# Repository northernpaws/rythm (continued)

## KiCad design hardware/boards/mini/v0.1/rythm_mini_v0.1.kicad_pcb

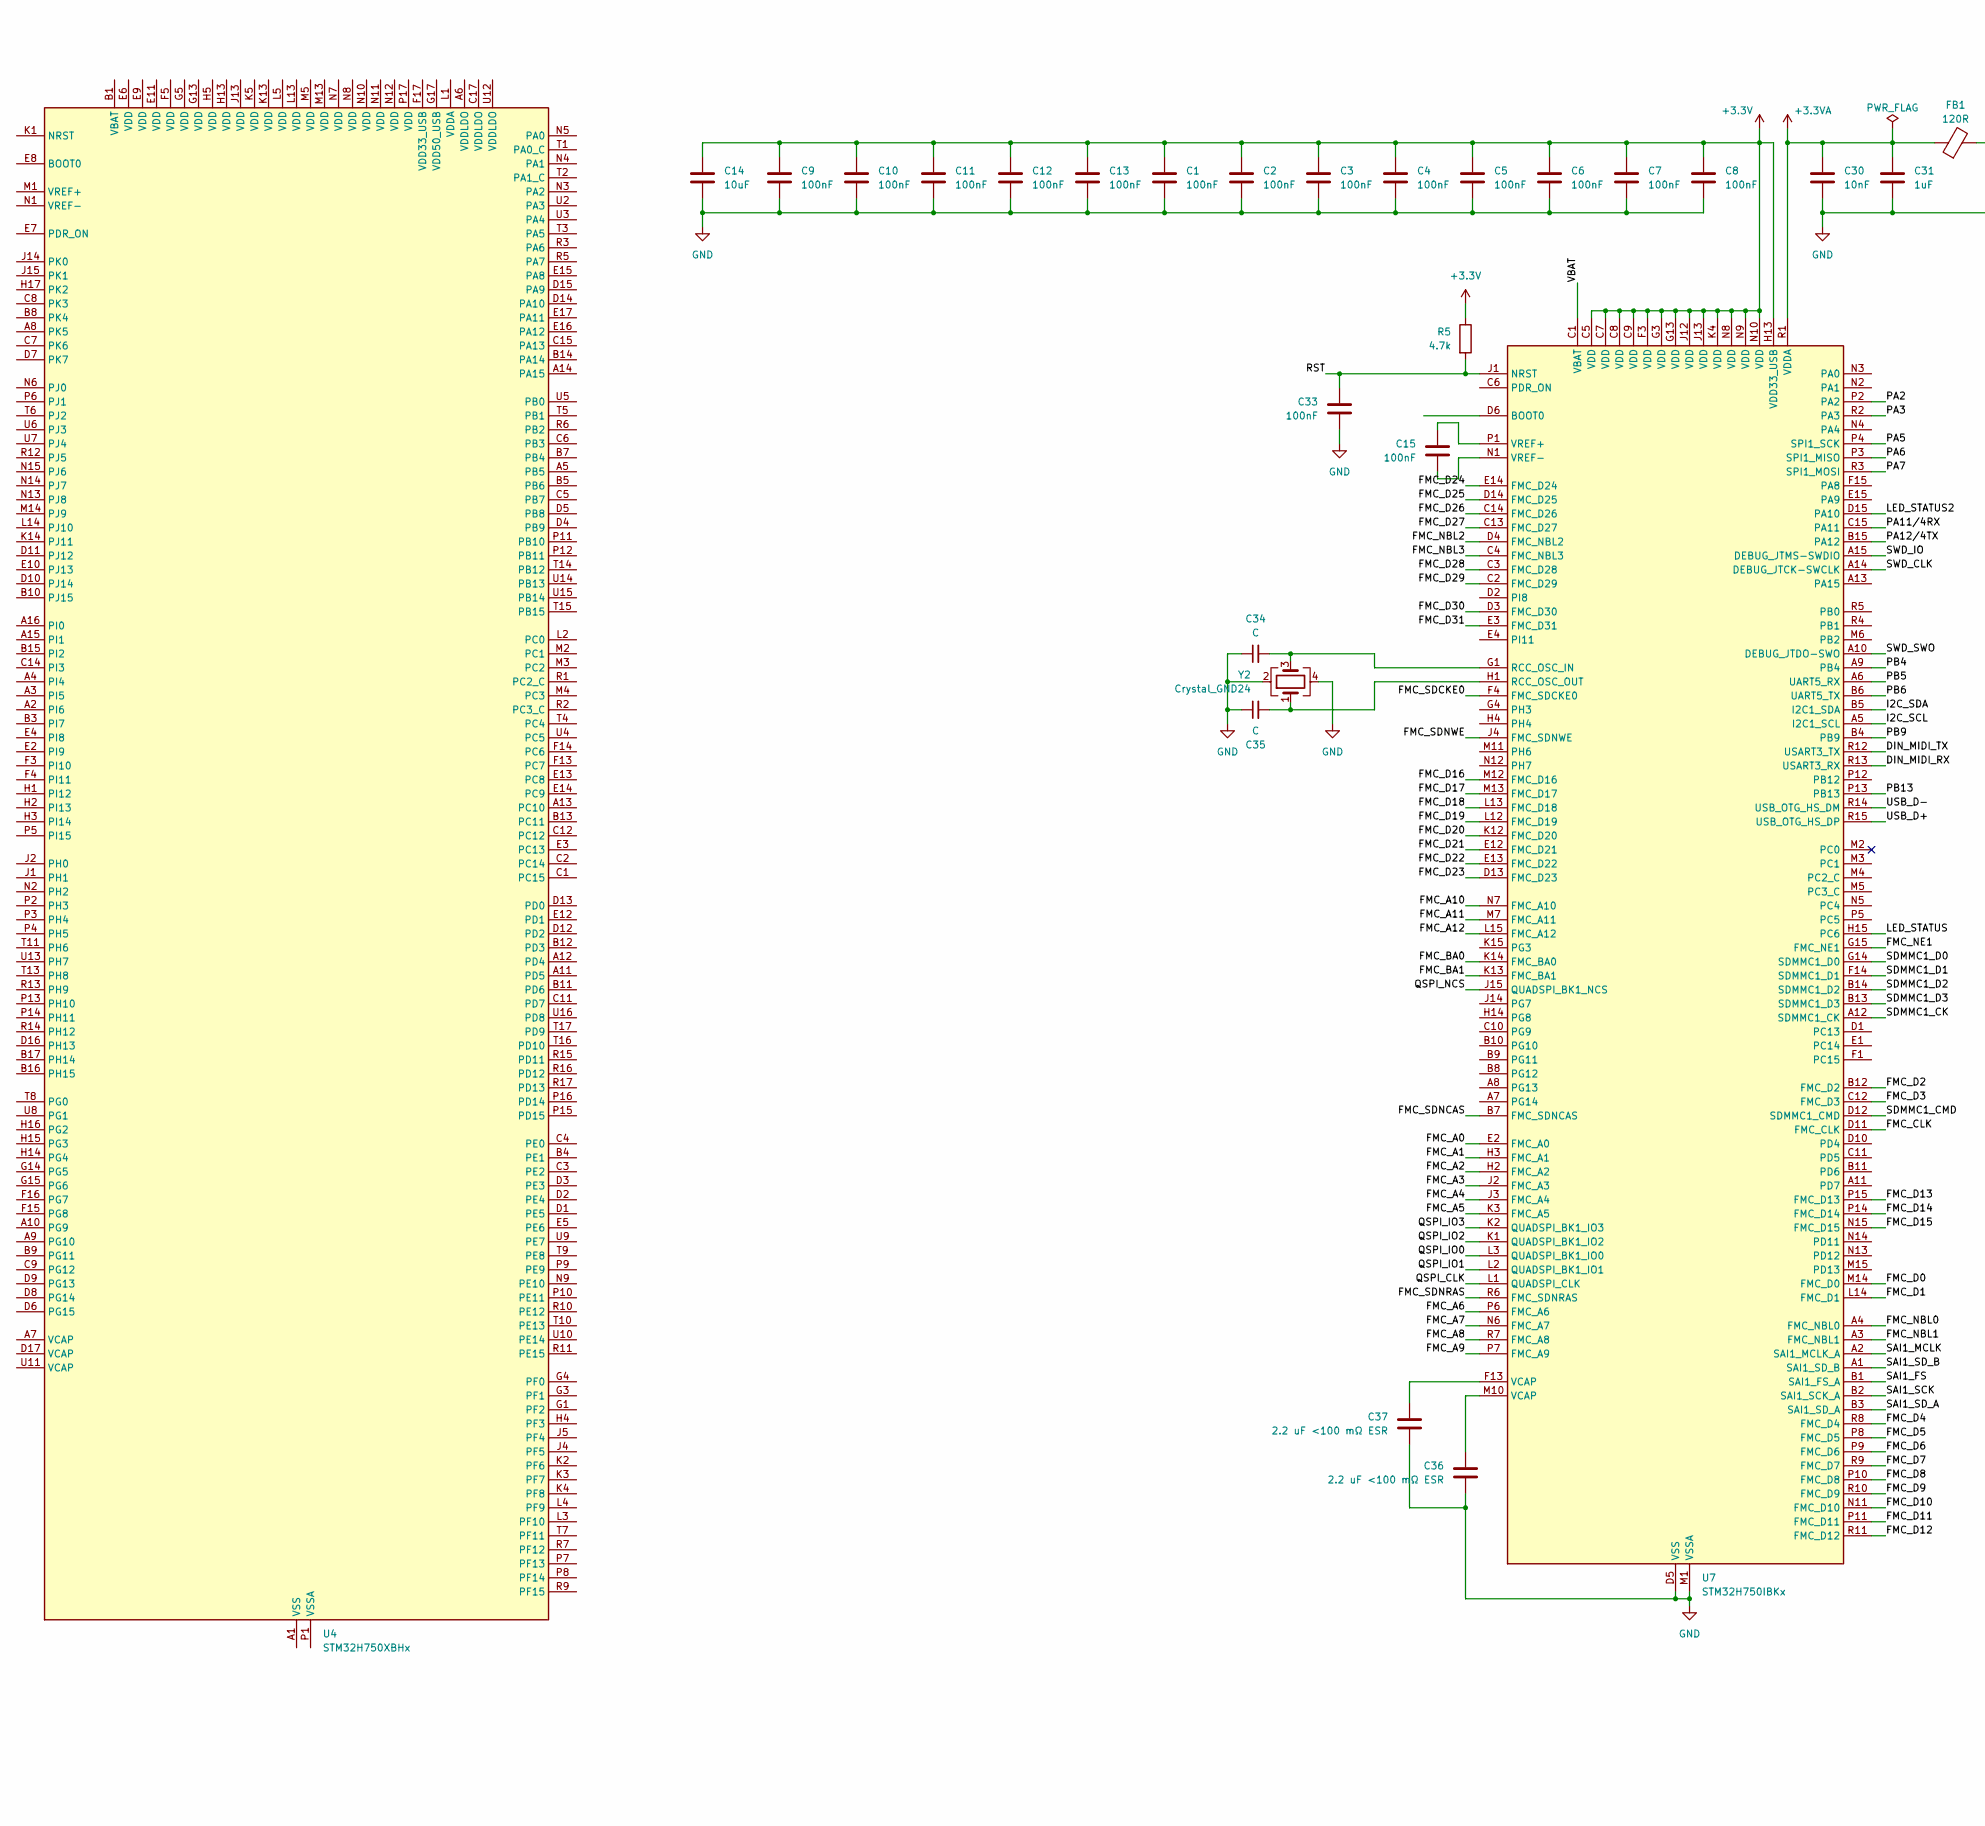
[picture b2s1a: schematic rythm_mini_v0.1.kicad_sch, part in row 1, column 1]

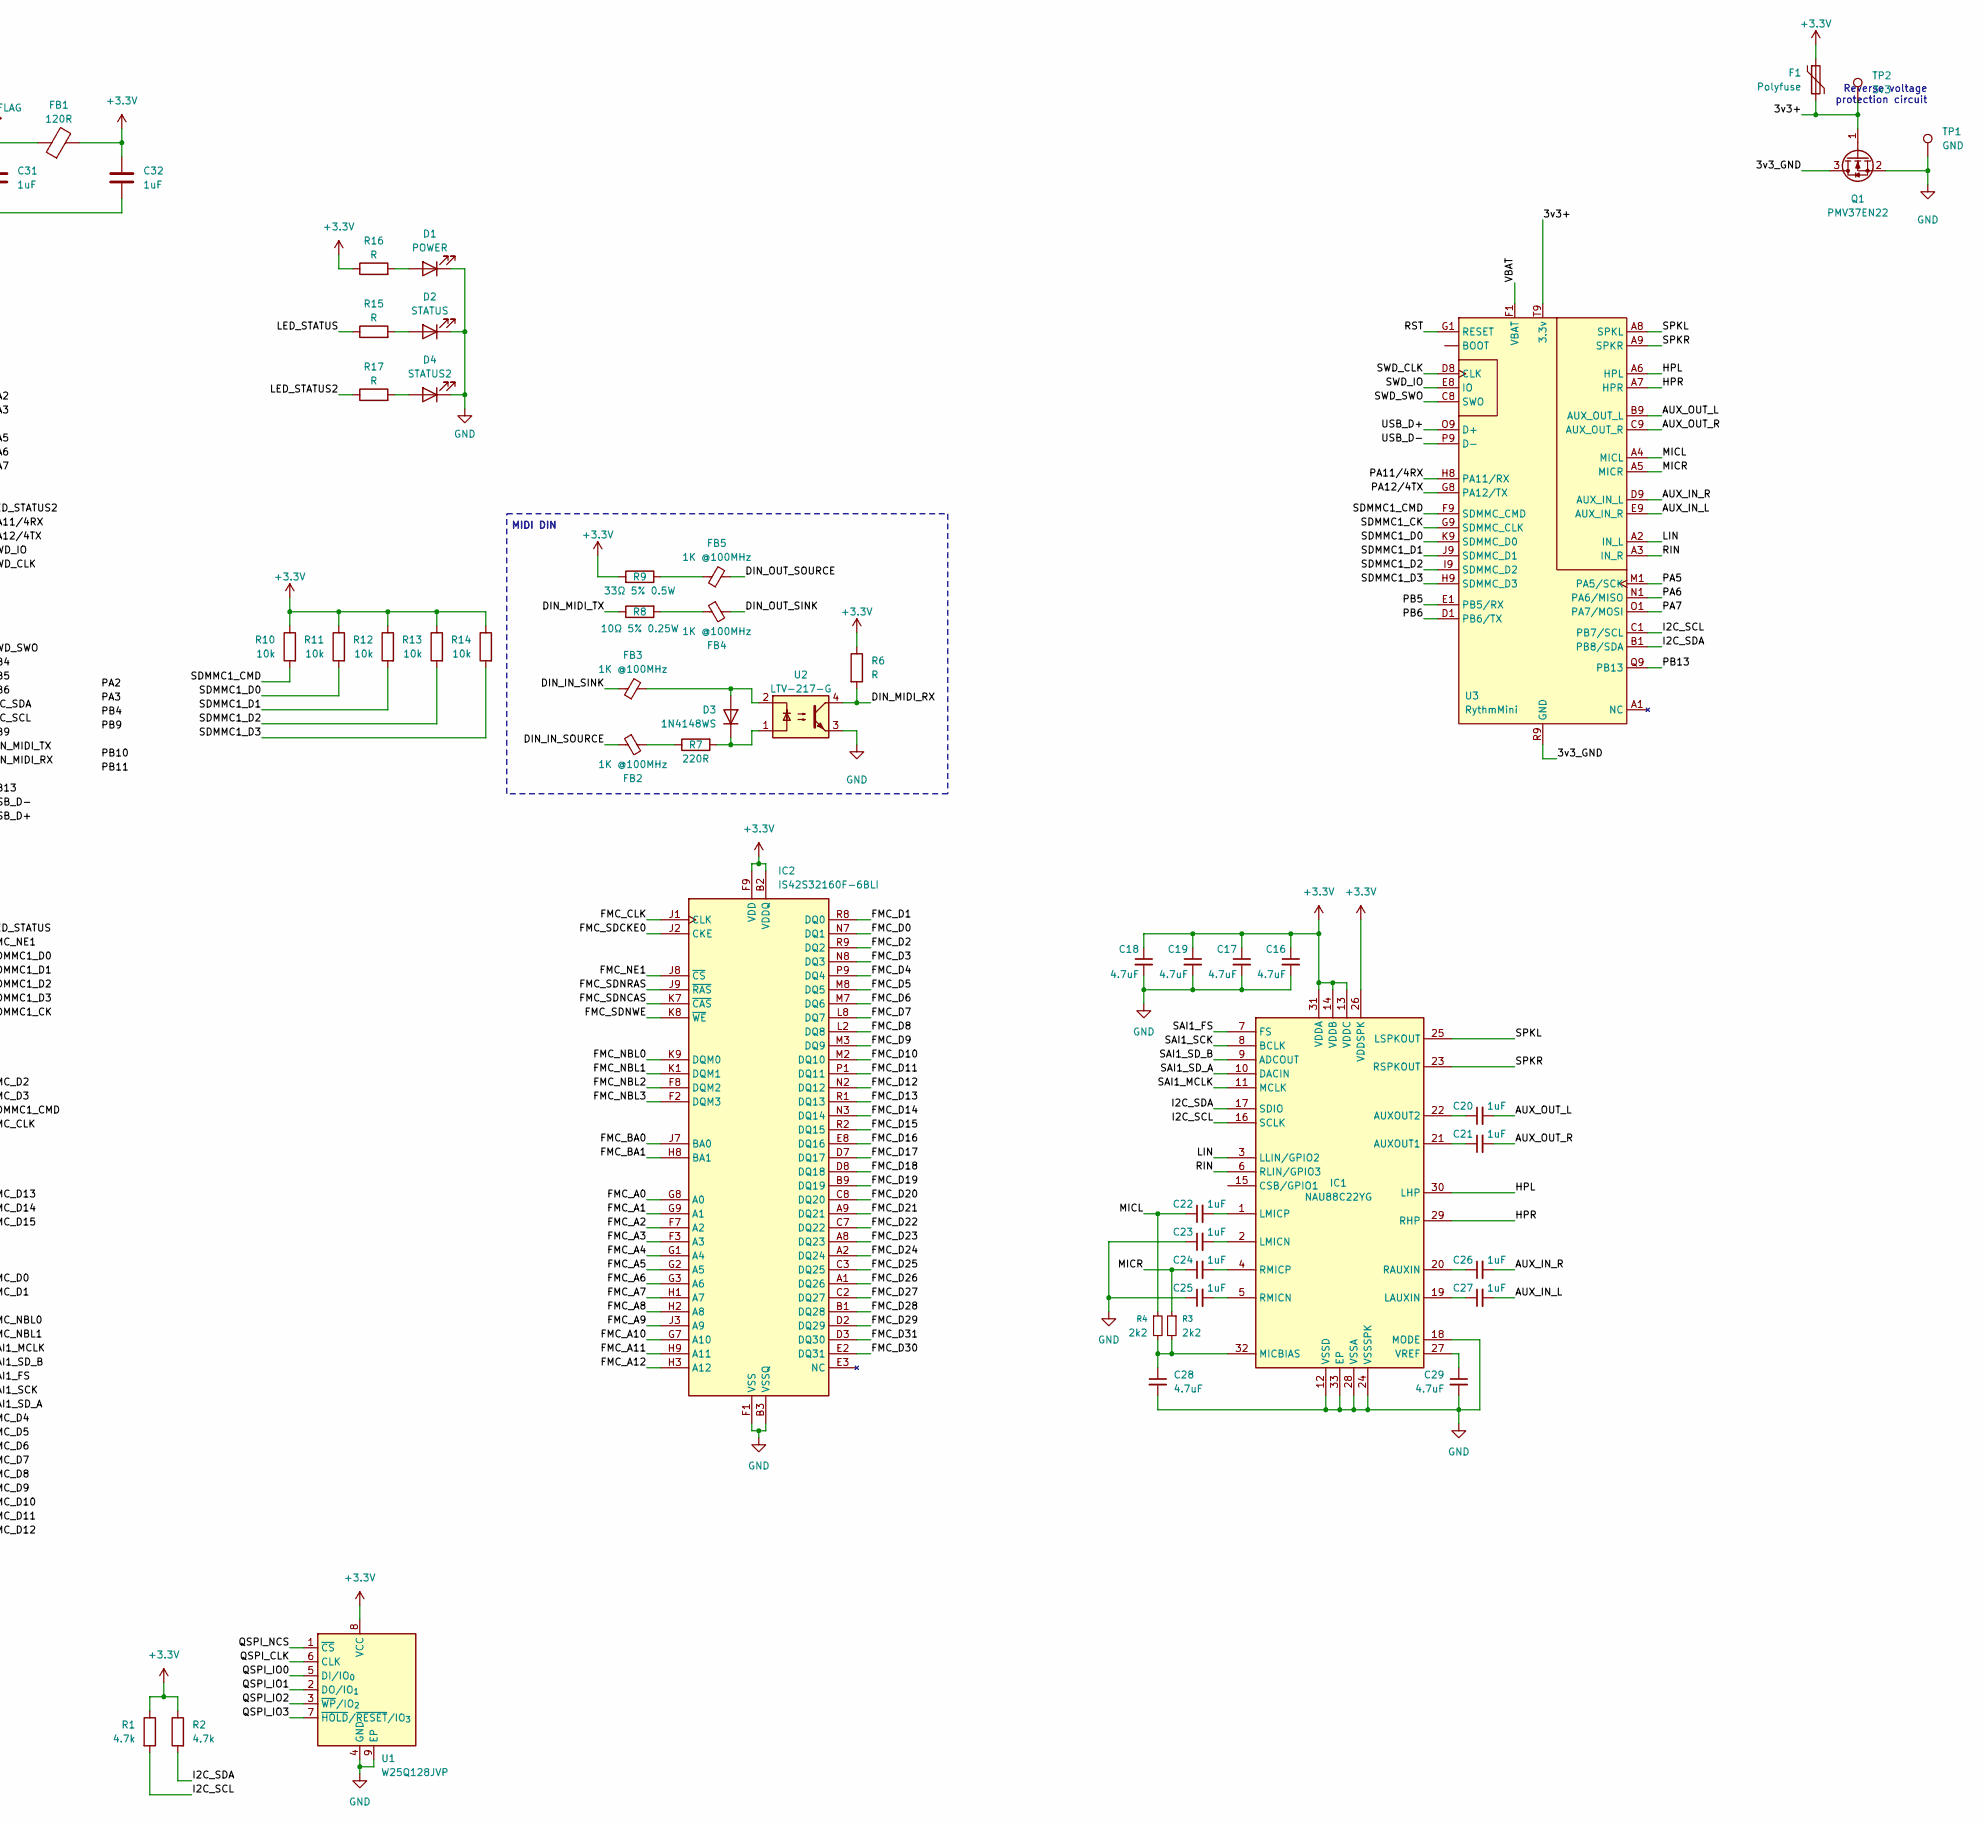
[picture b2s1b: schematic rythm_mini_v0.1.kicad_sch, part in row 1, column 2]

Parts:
C1, C2, C3, C4, C5, C6, C7, C8, C9, C10, C11, C12, C13, C15, C33: 100nF; C_0402_1005Metric
C14: 10uF; C_0402_1005Metric
C16, C17, C18, C19, C28, C29: 4.7uF; C_0402_1005Metric
C20, C21, C22, C23, C24, C25, C26, C27, C31, C32: 1uF; C_0402_1005Metric
C30: 10nF; C_0402_1005Metric
C34, C35: C
C36, C37: 2.2 uF <100 mΩ ESR; C_0402_1005Metric
D1: POWER; LED_0402_1005Metric
D2: STATUS; LED_0402_1005Metric
D3: 1N4148WS; D_SOD-323; JLC C2128
D4: STATUS2; LED_0402_1005Metric
F1: Polyfuse; Fuse_0805_2012Metric
FB1: 120R; L_0805_2012Metric
FB2, FB3, FB4, FB5: 1K @100MHz; L_0603_1608Metric
IC1: NAU88C22YG; QFN50P500X500X80-33N; Mouser Part Number 503-NAU88C22YG
IC2: IS42S32160F-6BLI; BGA90C80P9X15_800X1300X120; Mouser Part Number 870-IS42S32160F-6BLI
Q1: PMV37EN22; TSOT-23
R1, R2: 4.7k; R_0402_1005Metric
R3, R4: 2k2; R_0402_1005Metric
R5: 4.7k; C_0402_1005Metric
R6, R15, R16, R17: R; R_0402_1005Metric
R7: 220R; R_0402_1005Metric
R8: 10Ω 5% 0.25W; R_0402_1005Metric
R9: 33Ω 5% 0.5W; R_0402_1005Metric
R10, R11, R12, R13, R14: 10k; R_0402_1005Metric
TP1: GND; TestPoint_Pad_D1.0mm
TP2: 3v3; TestPoint_Pad_D1.0mm
U1: W25Q128JVP; WSON-8-1EP_6x5mm_P1.27mm_EP3.4x4.3mm; JLC C190862
U2: LTV-217-G; SOIC-4_4.55x2.6mm_P1.27mm; JLC C17407902
U3: RythmMini; RythmMini-v0.1
U4: STM32H750XBHx; TFBGA-265_14x14mm_Layout17x17_P0.8mm
U7: STM32H750IBKx; UFBGA-201_10x10mm_Layout15x15_P0.65mm; JLC C730200
Y2: Crystal_GND24; Crystal_SMD_Abracon_ABM10-4Pin_2.5x2.0mm

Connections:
+3.3V: C1.1, C2.1, C3.1, C4.1, C5.1, C6.1, C7.1, C8.1, C9.1, C10.1, C11.1, C12.1, C13.1, C14.1, C16.1, C17.1, C18.1, C19.1, C32.1, F1.1, FB1.2, IC1.13 (VDDC), IC1.14 (VDDB), IC1.26 (VDDSPK), IC1.31 (VDDA), IC2.A7 (VDD), IC2.B2 (VDDQ), IC2.B7 (VDDQ), IC2.C9 (VDDQ), IC2.D9 (VDDQ), IC2.E1 (VDDQ), IC2.F9 (VDD), IC2.L1 (VDDQ), IC2.L7 (VDD), IC2.M9 (VDDQ), IC2.N9 (VDDQ), IC2.P2 (VDDQ), IC2.P7 (VDDQ), IC2.R7 (VDD), R1.1, R2.1, R5.1, R6.1, R9.2, R10.1, R11.1, R12.1, R13.1, R14.1, R16.1, U1.8 (VCC), U7.C5 (VDD), U7.C7 (VDD), U7.C8 (VDD), U7.C9 (VDD), U7.F3 (VDD), U7.G3 (VDD), U7.G13 (VDD), U7.H13 (VDD33_USB), U7.J12 (VDD), U7.J13 (VDD), U7.K4 (VDD), U7.N8 (VDD), U7.N9 (VDD), U7.N10 (VDD)
+3.3VA: C30.1, C31.1, FB1.1, U7.R1 (VDDA)
/3v3+: F1.2, Q1.1 (G), TP2.1, U3.T9 (3.3v)
/3v3_GND: Q1.3 (D), U3.R9 (GND)
/AUX_IN_L: C27.2, U3.E9 (AUX_IN_R)
/AUX_IN_R: C26.2, U3.D9 (AUX_IN_L)
/AUX_OUT_L: C20.2, U3.B9 (AUX_OUT_L)
/AUX_OUT_R: C21.2, U3.C9 (AUX_OUT_R)
/DIN_IN_SINK: FB3.1
/DIN_IN_SOURCE: FB2.1
/DIN_MIDI_RX: R6.2, U2.4, U7.R13 (USART3_RX)
/DIN_MIDI_TX: R8.1, U7.R12 (USART3_TX)
/DIN_OUT_SINK: FB4.2
/DIN_OUT_SOURCE: FB5.2
/FMC_A0: IC2.G8 (A0), U7.E2 (FMC_A0)
/FMC_A1: IC2.G9 (A1), U7.H3 (FMC_A1)
/FMC_A2: IC2.F7 (A2), U7.H2 (FMC_A2)
/FMC_A3: IC2.F3 (A3), U7.J2 (FMC_A3)
/FMC_A4: IC2.G1 (A4), U7.J3 (FMC_A4)
/FMC_A5: IC2.G2 (A5), U7.K3 (FMC_A5)
/FMC_A6: IC2.G3 (A6), U7.P6 (FMC_A6)
/FMC_A7: IC2.H1 (A7), U7.N6 (FMC_A7)
/FMC_A8: IC2.H2 (A8), U7.R7 (FMC_A8)
/FMC_A9: IC2.J3 (A9), U7.P7 (FMC_A9)
/FMC_A10: IC2.G7 (A10), U7.N7 (FMC_A10)
/FMC_A11: IC2.H9 (A11), U7.M7 (FMC_A11)
/FMC_A12: IC2.H3 (A12), U7.L15 (FMC_A12)
/FMC_BA0: IC2.J7 (BA0), U7.K14 (FMC_BA0)
/FMC_BA1: IC2.H8 (BA1), U7.K13 (FMC_BA1)
/FMC_CLK: IC2.J1 (CLK), U7.D11 (FMC_CLK)
/FMC_D0: IC2.N7 (DQ1), U7.M14 (FMC_D0)
/FMC_D1: IC2.R8 (DQ0), U7.L14 (FMC_D1)
/FMC_D2: IC2.R9 (DQ2), U7.B12 (FMC_D2)
/FMC_D3: IC2.N8 (DQ3), U7.C12 (FMC_D3)
/FMC_D4: IC2.P9 (DQ4), U7.R8 (FMC_D4)
/FMC_D5: IC2.M8 (DQ5), U7.P8 (FMC_D5)
/FMC_D6: IC2.M7 (DQ6), U7.P9 (FMC_D6)
/FMC_D7: IC2.L8 (DQ7), U7.R9 (FMC_D7)
/FMC_D8: IC2.L2 (DQ8), U7.P10 (FMC_D8)
/FMC_D9: IC2.M3 (DQ9), U7.R10 (FMC_D9)
/FMC_D10: IC2.M2 (DQ10), U7.N11 (FMC_D10)
/FMC_D11: IC2.P1 (DQ11), U7.P11 (FMC_D11)
/FMC_D12: IC2.N2 (DQ12), U7.R11 (FMC_D12)
/FMC_D13: IC2.R1 (DQ13), U7.P15 (FMC_D13)
/FMC_D14: IC2.N3 (DQ14), U7.P14 (FMC_D14)
/FMC_D15: IC2.R2 (DQ15), U7.N15 (FMC_D15)
/FMC_D16: IC2.E8 (DQ16), U7.M12 (FMC_D16)
/FMC_D17: IC2.D7 (DQ17), U7.M13 (FMC_D17)
/FMC_D18: IC2.D8 (DQ18), U7.L13 (FMC_D18)
/FMC_D19: IC2.B9 (DQ19), U7.L12 (FMC_D19)
/FMC_D20: IC2.C8 (DQ20), U7.K12 (FMC_D20)
/FMC_D21: IC2.A9 (DQ21), U7.E12 (FMC_D21)
/FMC_D22: IC2.C7 (DQ22), U7.E13 (FMC_D22)
/FMC_D23: IC2.A8 (DQ23), U7.D13 (FMC_D23)
/FMC_D24: IC2.A2 (DQ24), U7.E14 (FMC_D24)
/FMC_D25: IC2.C3 (DQ25), U7.D14 (FMC_D25)
/FMC_D26: IC2.A1 (DQ26), U7.C14 (FMC_D26)
/FMC_D27: IC2.C2 (DQ27), U7.C13 (FMC_D27)
/FMC_D28: IC2.B1 (DQ28), U7.C3 (FMC_D28)
/FMC_D29: IC2.D2 (DQ29), U7.C2 (FMC_D29)
/FMC_D30: IC2.E2 (DQ31), U7.D3 (FMC_D30)
/FMC_D31: IC2.D3 (DQ30), U7.E3 (FMC_D31)
/FMC_NBL0: IC2.K9 (DQM0), U7.A4 (FMC_NBL0)
/FMC_NBL1: IC2.K1 (DQM1), U7.A3 (FMC_NBL1)
/FMC_NBL2: IC2.F8 (DQM2), U7.D4 (FMC_NBL2)
/FMC_NBL3: IC2.F2 (DQM3), U7.C4 (FMC_NBL3)
/FMC_NE1: IC2.J8 (~CS), U7.G15 (FMC_NE1)
/FMC_SDCKE0: IC2.J2 (CKE), U7.F4 (FMC_SDCKE0)
/FMC_SDNCAS: IC2.K7 (~CAS), U7.B7 (FMC_SDNCAS)
/FMC_SDNRAS: IC2.J9 (~RAS), U7.R6 (FMC_SDNRAS)
/FMC_SDNWE: IC2.K8 (~WE), U7.J4 (FMC_SDNWE)
/HPL: IC1.30 (LHP), U3.A6 (HPL)
/HPR: IC1.29 (RHP), U3.A7 (HPR)
/I2C_SCL: IC1.16 (SCLK), R1.2, U3.C1 (PB7/SCL), U7.A5 (I2C1_SCL)
/I2C_SDA: IC1.17 (SDIO), R2.2, U3.B1 (PB8/SDA), U7.B5 (I2C1_SDA)
/LED_STATUS: R15.1, U7.H15 (PC6)
/LED_STATUS2: R17.1, U7.D15 (PA10)
/LIN: IC1.3 (LLIN/GPIO2), U3.A2 (IN_L)
/MICL: C22.1, R4.1, U3.A4 (MICL)
/MICR: C24.1, R3.1, U3.A5 (MICR)
/PA2: U7.P2 (PA2)
/PA3: U7.R2 (PA3)
/PA5: U3.M1 (PA5/SCK), U7.P4 (SPI1_SCK)
/PA6: U3.N1 (PA6/MISO), U7.P3 (SPI1_MISO)
/PA7: U3.O1 (PA7/MOSI), U7.R3 (SPI1_MOSI)
/PA11/4RX: U3.H8 (PA11/RX), U7.C15 (PA11)
/PA12/4TX: U3.G8 (PA12/TX), U7.B15 (PA12)
/PB4: U7.A9 (PB4)
/PB5: U3.E1 (PB5/RX), U7.A6 (UART5_RX)
/PB6: U3.D1 (PB6/TX), U7.B6 (UART5_TX)
/PB9: U7.B4 (PB9)
/PB13: U3.Q9 (PB13), U7.P13 (PB13)
/QSPI_CLK: U1.6 (CLK), U7.L1 (QUADSPI_CLK)
/QSPI_IO0: U1.5 (DI/IO_{0}), U7.L3 (QUADSPI_BK1_IO0)
/QSPI_IO1: U1.2 (DO/IO_{1}), U7.L2 (QUADSPI_BK1_IO1)
/QSPI_IO2: U1.3 (~WP/IO_{2}), U7.K1 (QUADSPI_BK1_IO2)
/QSPI_IO3: U1.7 (~HOLD/~RESET/IO_{3}), U7.K2 (QUADSPI_BK1_IO3)
/QSPI_NCS: U1.1 (~CS), U7.J15 (QUADSPI_BK1_NCS)
/RIN: IC1.6 (RLIN/GPIO3), U3.A3 (IN_R)
/RST: C33.1, R5.2, U3.G1 (RESET), U7.J1 (NRST)
/SAI1_FS: IC1.7 (FS), U7.B1 (SAI1_FS_A)
/SAI1_MCLK: IC1.11 (MCLK), U7.A2 (SAI1_MCLK_A)
/SAI1_SCK: IC1.8 (BCLK), U7.B2 (SAI1_SCK_A)
/SAI1_SD_A: IC1.10 (DACIN), U7.B3 (SAI1_SD_A)
/SAI1_SD_B: IC1.9 (ADCOUT), U7.A1 (SAI1_SD_B)
/SDMMC1_CK: U3.G9 (SDMMC_CLK), U7.A12 (SDMMC1_CK)
/SDMMC1_CMD: R10.2, U3.F9 (SDMMC_CMD), U7.D12 (SDMMC1_CMD)
/SDMMC1_D0: R11.2, U3.K9 (SDMMC_D0), U7.G14 (SDMMC1_D0)
/SDMMC1_D1: R12.2, U3.J9 (SDMMC_D1), U7.F14 (SDMMC1_D1)
/SDMMC1_D2: R13.2, U3.I9 (SDMMC_D2), U7.B14 (SDMMC1_D2)
/SDMMC1_D3: R14.2, U3.H9 (SDMMC_D3), U7.B13 (SDMMC1_D3)
/SPKL: IC1.25 (LSPKOUT), U3.A8 (SPKL)
/SWD_CLK: U3.D8 (CLK), U7.A14 (DEBUG_JTCK-SWCLK)
/SWD_IO: U3.E8 (IO), U7.A15 (DEBUG_JTMS-SWDIO)
/SWD_SWO: U3.C8 (SWO), U7.A10 (DEBUG_JTDO-SWO)
/USB_D+: U3.O9 (D+), U7.R15 (USB_OTG_HS_DP)
/USB_D-: U3.P9 (D-), U7.R14 (USB_OTG_HS_DM)
/VBAT: U3.F1 (VBAT), U7.C1 (VBAT)
GND: C1.2, C2.2, C3.2, C4.2, C5.2, C6.2, C7.2, C8.2, C9.2, C10.2, C11.2, C12.2, C13.2, C14.2, C16.2, C17.2, C18.2, C19.2, C23.1, C25.1, C28.2, C29.2, C30.2, C31.2, C32.2, C33.2, C34.1, C35.1, C36.2, C37.2, D1.1 (K), D2.1 (K), D4.1 (K), IC1.12 (VSSD), IC1.18 (MODE), IC1.24 (VSSSPK), IC1.28 (VSSA), IC1.33 (EP), IC2.A3 (VSS), IC2.B3 (VSSQ), IC2.B8 (VSSQ), IC2.C1 (VSSQ), IC2.D1 (VSSQ), IC2.E9 (VSSQ), IC2.F1 (VSS), IC2.L3 (VSS), IC2.L9 (VSSQ), IC2.M1 (VSSQ), IC2.N1 (VSSQ), IC2.P3 (VSSQ), IC2.P8 (VSSQ), IC2.R3 (VSS), Q1.2 (S), TP1.1, U1.4 (GND), U1.9 (EP), U2.3, U4.N3 (PA2), U7.D5 (VSS), U7.D7 (VSS), U7.D8 (VSS), U7.D9 (VSS), U7.F2 (VSS), U7.F6 (VSS), U7.F7 (VSS), U7.F8 (VSS), U7.F9 (VSS), U7.F10 (VSS), U7.F12 (VSS), U7.G2 (VSS), U7.G6 (VSS), U7.G7 (VSS), U7.G8 (VSS), U7.G9 (VSS), U7.G10 (VSS), U7.G12 (VSS), U7.H6 (VSS), U7.H7 (VSS), U7.H8 (VSS), U7.H9 (VSS), U7.H10 (VSS), U7.H12 (VSS), U7.J6 (VSS), U7.J7 (VSS), U7.J8 (VSS), U7.J9 (VSS), U7.J10 (VSS), U7.K6 (VSS), U7.K7 (VSS), U7.K8 (VSS), U7.K9 (VSS), U7.K10 (VSS), U7.L4 (VSS), U7.M1 (VSSA), U7.M8 (VSS), U7.M9 (VSS), Y2.2, Y2.4
unnamed: C36.1, U7.M10 (VCAP)
unnamed: C37.1, U7.F13 (VCAP)
unnamed: D1.2 (A), R16.2
unnamed: D2.2 (A), R15.2
unnamed: D3.2 (A), FB3.2, U2.2
unnamed: D3.1 (K), R7.2, U2.1
unnamed: D4.2 (A), R17.2
unnamed: FB2.2, R7.1
unnamed: FB4.1, R8.2
unnamed: FB5.1, R9.1
unnamed: C21.1, IC1.21 (AUXOUT1)
unnamed: C20.1, IC1.22 (AUXOUT2)
unnamed: C27.1, IC1.19 (LAUXIN)
unnamed: C23.2, IC1.2 (LMICN)
unnamed: C22.2, IC1.1 (LMICP)
unnamed: C28.1, IC1.32 (MICBIAS), R3.2, R4.2
unnamed: C26.1, IC1.20 (RAUXIN)
unnamed: C25.2, IC1.5 (RMICN)
unnamed: C24.2, IC1.4 (RMICP)
unnamed: C29.1, IC1.27 (VREF)
unnamed: U4.A1 (VSS), U4.A17 (VSS), U4.B2 (VSS), U4.B6 (VSS), U4.C10 (VSS), U4.C13 (VSS), U4.C16 (VSS), U4.F1 (VSS), U4.F2 (VSS), U4.G2 (VSS), U4.G7 (VSS), U4.G8 (VSS), U4.G9 (VSS), U4.G10 (VSS), U4.G11 (VSS), U4.G16 (VSS), U4.H7 (VSS), U4.H8 (VSS), U4.H9 (VSS), U4.H10 (VSS), U4.H11 (VSS), U4.J3 (VSS), U4.J7 (VSS), U4.J8 (VSS), U4.J9 (VSS), U4.J10 (VSS), U4.J11 (VSS), U4.J16 (VSS), U4.J17 (VSS), U4.K7 (VSS), U4.K8 (VSS), U4.K9 (VSS), U4.K10 (VSS), U4.K11 (VSS), U4.K15 (VSS), U4.L7 (VSS), U4.L8 (VSS), U4.L9 (VSS), U4.L10 (VSS), U4.L11 (VSS), U4.L15 (VSS), U4.M15 (VSS), U4.N16 (VSS), U4.R4 (VSS), U4.R8 (VSS), U4.T12 (VSS), U4.U1 (VSS), U4.U17 (VSS)
unnamed: C34.2, U7.G1 (RCC_OSC_IN), Y2.3
unnamed: C35.2, U7.H1 (RCC_OSC_OUT), Y2.1
unnamed: C15.1, U7.P1 (VREF+)
unnamed: C15.2, U7.N1 (VREF-)

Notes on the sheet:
MIDI DIN
Reverse voltage protection circuit

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
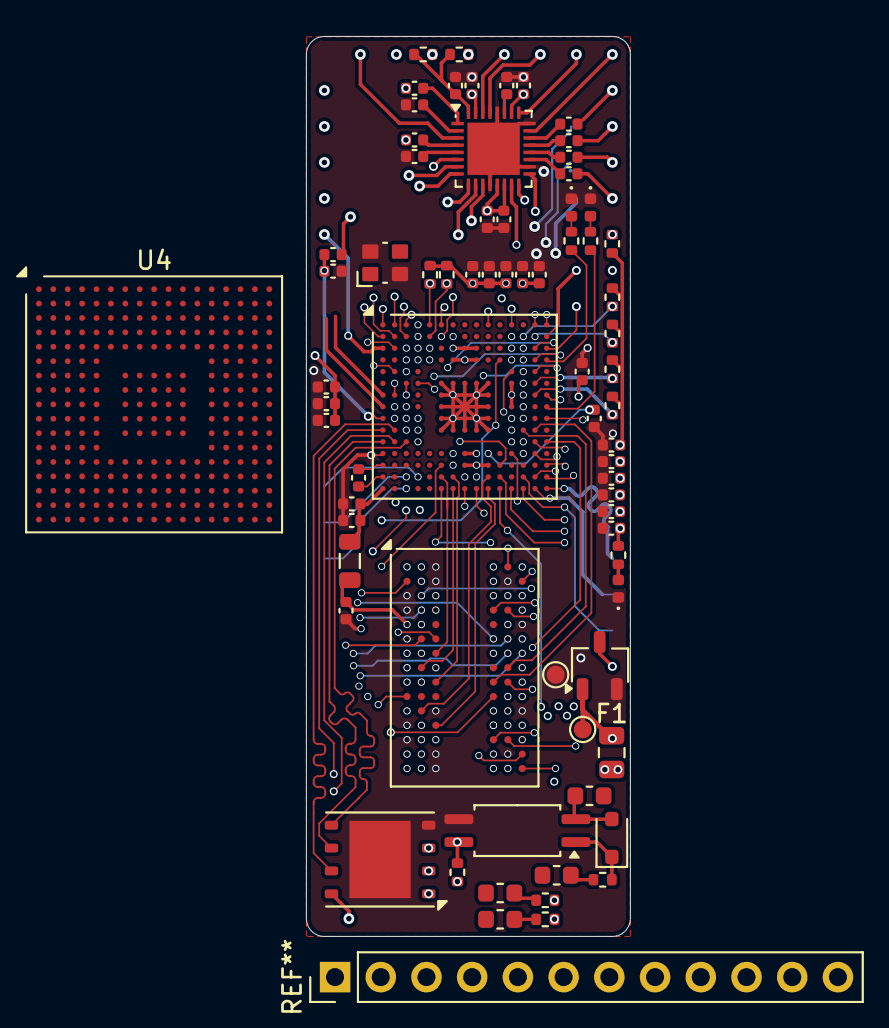
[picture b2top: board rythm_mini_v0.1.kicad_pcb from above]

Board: 8 copper layers, 18.0 x 50.0 mm, 73 parts (0 on the bottom side), 137 nets.

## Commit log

2025-11-26 mini: route qspi flash and add more brakeout pads
2025-11-30 re-routing audio codec
2025-11-30 start adding README.md
2025-12-01 start implementing audio buffer and sine oscillator
2025-12-03 start rev2 of mini module with larger BGA package
2025-12-04 testing routing layout on card board
2025-12-09 fix instrument sample trait bounds
2025-12-09 update sine synth example to use per-voice timebase
2025-12-10 migrate sine-instrument example to unified oscillator framework
2025-12-11 implement lookup table oscillator and `Frequency` type
2025-12-11 basic `sine-synth` example mostly working
2025-12-11 add global scaling to `sine-synth` example instead of voice-dependent scaling
2025-12-11 add note about `sine-synth` amplitude scaling
2025-12-11 simplify `sine-synth` voice summing
2025-12-11 add README.md to `sine-synth` example
2025-12-11 document `sine-synth` example code
2025-12-12 move `engine` create into `crates` folder
2025-12-12 minor module routing cleanup
2025-12-13 mini: test routing of x32 as x16
2025-12-14 mini: route top mezzanine connector
2025-12-14 mini: add SDRAM decoupling
2025-12-14 mini: downsized mezzanine from 70 pin to 60
2025-12-15 mini: clean up routing around codec
2025-12-15 put images side-by-side in README.md
2025-12-16 add descriptions of kits to README.md
2025-12-16 mini: more GPIO routing, added OSC32 oscillator
2025-12-16 mini: schematic organization
2025-12-16 mini: board layout cleanup
2025-12-16 mini: start BOM selection
2025-12-17 mini: add Digikey part numbers to BOM
2025-12-17 mini: layout adjustments after component package changes
2025-12-18 mini: rename project files
2025-12-20 mini: various routing cleanup
2025-12-20 add mini notes to README.md
2025-12-20 update README.md language to be consistent
2025-12-20 mini: add license identifier to silkscreen
2025-12-20 various updates to README.md
2025-12-20 add `.gitignore` for `bsp` crate
2025-12-20 mini: route power supply protections
2025-12-20 mini: start adding symbol for mating footprint
2025-12-20 add notes about dual connector Hirose DF40 configuration
2025-12-20 mini: start speculative v0.3 revision with single connector
2025-12-21 mini: SWD, SPI, and audio codec layout
2025-12-21 mini: add model for DF40 connector
2025-12-21 add 3cats to supporters list
2025-12-22 mini: change flash to SOIC8 to fix routing
2025-12-22 mini: more flash routing with new SOIC8 package
2025-12-22 apply catalina project name
2025-12-22 group crates under cargo workspace
2025-12-22 fix errors in instruments crate
2025-12-23 add GitHub FUNDING.yml
2025-12-23 fix Patreon funding entry format
2025-12-23 add cli tool foundations
2025-12-23 add missing feature flags for shadowed imports in root crate
2025-12-23 add note about rename in README.md
2025-12-23 add GitHub CI workflows for CLI and library
2025-12-23 correct names of CI workflows
2025-12-23 update READMEs and add licenses to crates
2025-12-23 update package descriptions
2025-12-23 change primary oscillator sampling methods to take phase instead of time index
2025-12-23 various crate documentation updates
2025-12-24 initial ADSR envelope implementation
2025-12-25 add missing attribution to variable wave oscillator
2025-12-25 adjust oscillator trait to use internal phase, and support rendering to a buffer
2025-12-25 move examples to root crate
2025-12-25 implement `Signal` trait on oscillators
2025-12-27 implement oscillator voices for additive synth sample
